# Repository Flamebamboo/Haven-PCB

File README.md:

# Haven Kuala Lumpur PCB Badge

So we got sponsored by PCBWay last minute and had only a few hours to design it so it could be shipped on time.
Here's what I made: A simple text book circuit but going details into the design and art. Since a lot of teenagers are not familiar with the use of PCB I decided to turn my art into a tutorial. There's an art for each components that you need for this PCB to work!

## Design photos

## Assembly and use

The design uses a CR2032 holder, a push button, a 3 mm LED and a 1 kΩ resistor. Use the board markings to place the parts and check the LED and battery-holder polarity before inserting the cell. Press the button to light the LED. J2 provides two optional solder points for battery leads.

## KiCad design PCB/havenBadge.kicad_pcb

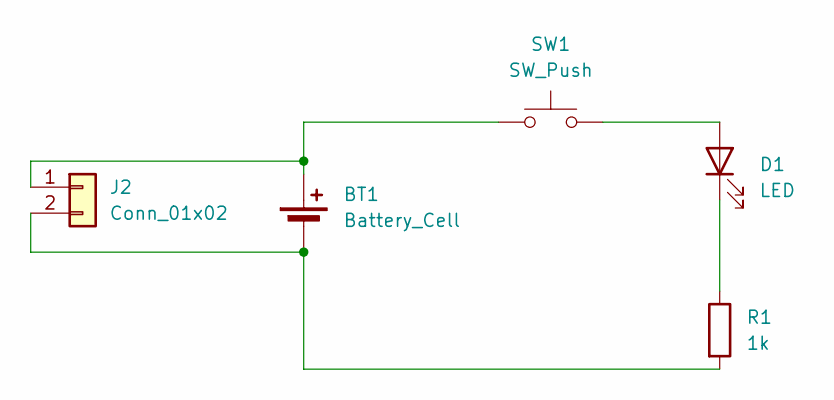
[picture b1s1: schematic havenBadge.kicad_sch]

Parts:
BT1: Battery_Cell; BatteryClip_CR2032_THT_P21.20mm
D1: LED; LED_D3.0mm
J2: Conn_01x02; PinHeader_1x02_P2.54mm_Vertical
R1: 1k; R_Axial_DIN0207_L6.3mm_D2.5mm_P7.62mm_Horizontal
SW1: SW_Push; SW_PUSH_6mm

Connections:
unnamed: BT1.1 (+), J2.1, SW1.1
unnamed: BT1.2 (-), J2.2, R1.2
unnamed: D1.2 (A), SW1.2
unnamed: D1.1 (K), R1.1

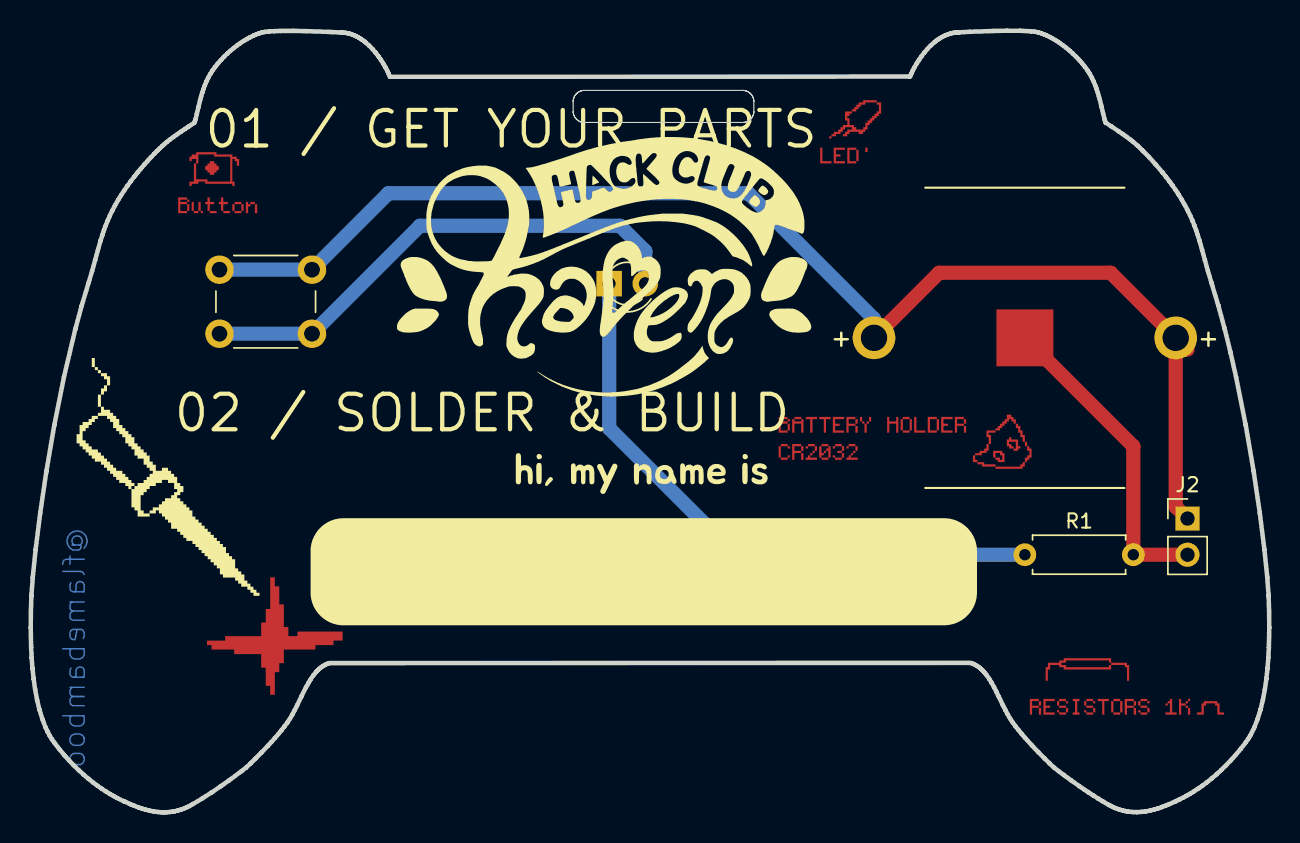
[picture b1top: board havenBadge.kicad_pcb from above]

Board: 2 copper layers, 87.0 x 54.9 mm, 5 parts (0 on the bottom side), 4 nets.
